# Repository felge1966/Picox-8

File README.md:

PicoX-8: Universalerweiterung für den Epson PX-8

https://forum.classic-computing.de/forum/index.php?thread/33295-picox-8-universalerweiterung-f%C3%BCr-den-epson-px-8/

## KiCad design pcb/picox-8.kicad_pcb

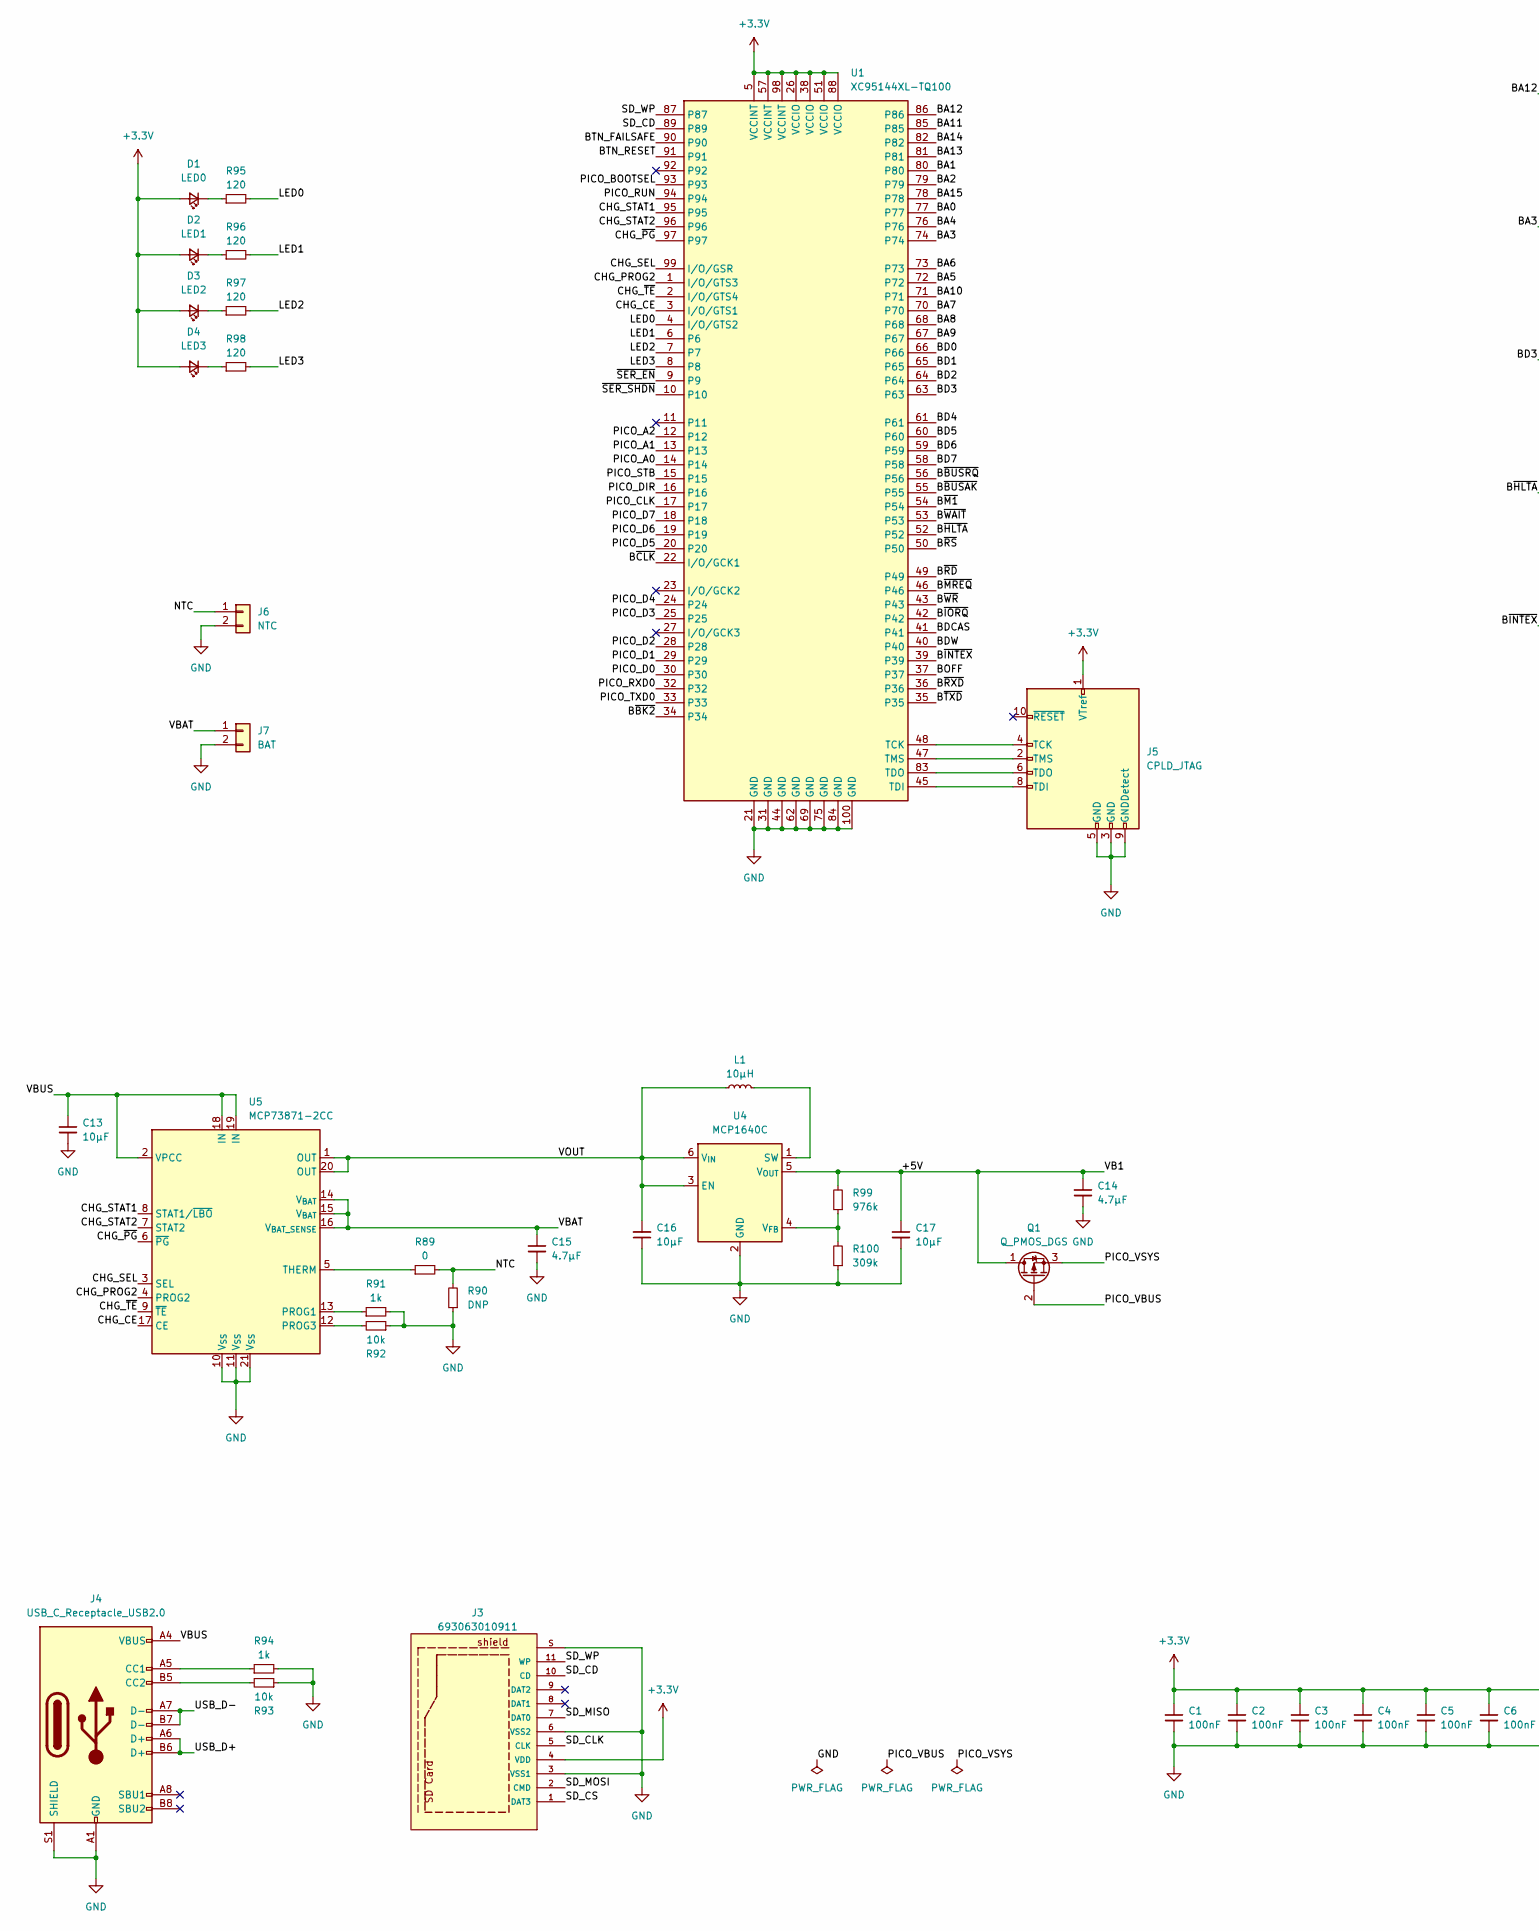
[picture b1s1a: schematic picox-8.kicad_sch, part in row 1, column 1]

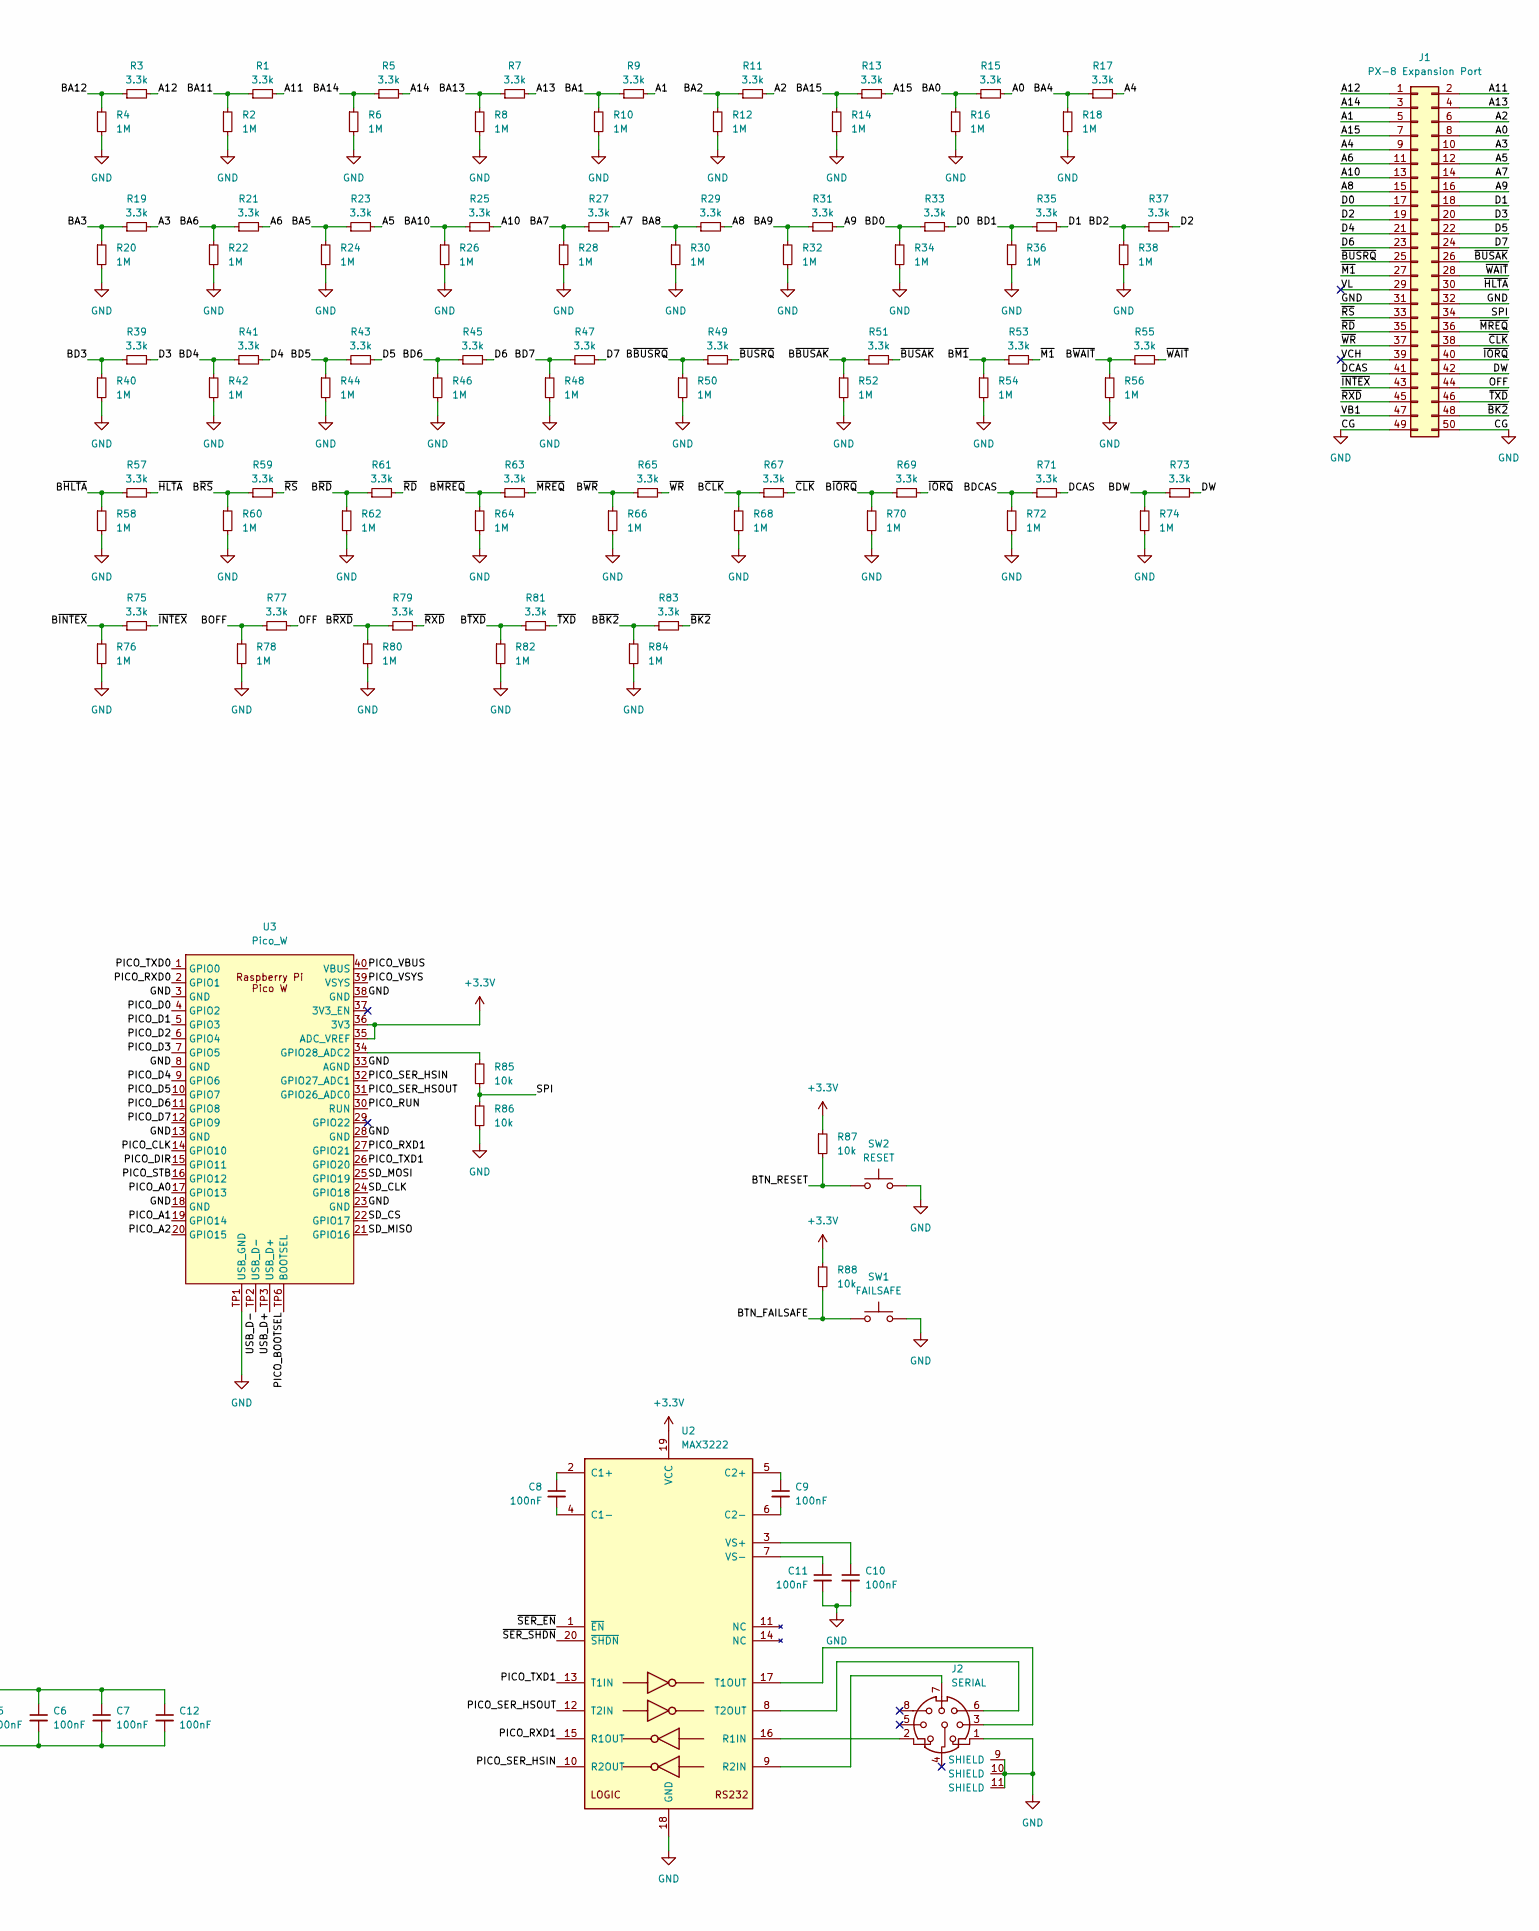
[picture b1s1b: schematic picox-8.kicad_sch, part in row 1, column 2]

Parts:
C1, C2, C3, C4, C5, C6, C7, C8, C9, C10, C11, C12: 100nF; C_0603_1608Metric_Pad1.08x0.95mm_HandSolder
C13, C16, C17: 10μF; C_0603_1608Metric_Pad1.08x0.95mm_HandSolder
C14, C15: 4.7μF; C_0603_1608Metric_Pad1.08x0.95mm_HandSolder
D1: LED0; LED_0603_1608Metric_Pad1.05x0.95mm_HandSolder
D2: LED1; LED_0603_1608Metric_Pad1.05x0.95mm_HandSolder
D3: LED2; LED_0603_1608Metric_Pad1.05x0.95mm_HandSolder
D4: LED3; LED_0603_1608Metric_Pad1.05x0.95mm_HandSolder
J1: PX-8 Expansion Port; IDC-Header_2x25_P2.54mm_Latch_Horizontal
J2: SERIAL; minidin-8
J3: 693063010911; Wuerth SD Card 693063010911; PART-NUMBER 693063010911
J4: USB_C_Receptacle_USB2.0; USB_C_Receptacle_G-Switch_GT-USB-7010ASV
J5: CPLD_JTAG; IDC-Header_2x05_P2.54mm_Vertical
J6: NTC; PinHeader_1x02_P2.54mm_Vertical
J7: BAT; JST_EH_S2B-EH_1x02_P2.50mm_Horizontal
L1: 10µH; L_Radial_D6.0mm_P4.00mm
Q1: Q_PMOS_DGS; SOT-23-3
R1, R3, R5, R7, R9, R11, R13, R15, R17, R19, R21, R23, R25, R27, R29, R31, R33, R35, R37, R39, R41, R43, R45, R47, R49, R51, R53, R55, R57, R59, R61, R63, R65, R67, R69, R71, R73, R75, R77, R79, R81, R83: 3.3k; R_0603_1608Metric_Pad0.98x0.95mm_HandSolder
R2, R4, R6, R8, R10, R12, R14, R16, R18, R20, R22, R24, R26, R28, R30, R32, R34, R36, R38, R40, R42, R44, R46, R48, R50, R52, R54, R56, R58, R60, R62, R64, R66, R68, R70, R72, R74, R76, R78, R80, R82, R84: 1M; R_0603_1608Metric_Pad0.98x0.95mm_HandSolder
R85, R86, R87, R88, R92, R93: 10k; R_0603_1608Metric_Pad0.98x0.95mm_HandSolder
R89: 0; R_0603_1608Metric_Pad0.98x0.95mm_HandSolder
R90: DNP; R_0603_1608Metric_Pad0.98x0.95mm_HandSolder
R91, R94: 1k; R_0603_1608Metric_Pad0.98x0.95mm_HandSolder
R95, R96, R97, R98: 120; R_0603_1608Metric_Pad0.98x0.95mm_HandSolder
R99: 976k; R_0603_1608Metric_Pad0.98x0.95mm_HandSolder
R100: 309k; R_0603_1608Metric_Pad0.98x0.95mm_HandSolder
SW1: FAILSAFE; SW_Tactile_SPST_Angled_PTS645Vx39-2LFS
SW2: RESET; SW_Tactile_SPST_Angled_PTS645Vx39-2LFS
U1: XC95144XL-TQ100; TQFP-100_14x14mm_P0.5mm
U2: MAX3222; TSSOP-20_4.4x6.5mm_P0.65mm
U3: Pico_W; RPI Pico W USB and Prog
U4: MCP1640C; SOT-23-6
U5: MCP73871-2CC; QFN-20-1EP_4x4mm_P0.5mm_EP2.5x2.5mm

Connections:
+3.3V: C1.1, C2.1, C3.1, C4.1, C5.1, C6.1, C7.1, C12.1, D1.2 (A), D2.2 (A), D3.2 (A), D4.2 (A), J3.4 (VDD), J5.1 (VTref), R87.1, R88.1, U1.5 (VCCINT), U1.26 (VCCIO), U1.38 (VCCIO), U1.51 (VCCIO), U1.57 (VCCINT), U1.88 (VCCIO), U1.98 (VCCINT), U2.19 (VCC), U3.35 (ADC_VREF), U3.36 (3V3)
/+5V: C14.1, C17.1, J1.47 (VB1), Q1.1 (D), R99.2, U4.5 (V_{OUT})
/A0: J1.8 (A0), R15.2
/A1: J1.5 (A1), R9.2
/A2: J1.6 (A2), R11.2
/A3: J1.10 (A3), R19.2
/A4: J1.9 (A4), R17.2
/A5: J1.12 (A5), R23.2
/A6: J1.11 (A6), R21.2
/A7: J1.14 (A7), R27.2
/A8: J1.15 (A8), R29.2
/A9: J1.16 (A9), R31.2
/A10: J1.13 (A10), R25.2
/A11: J1.2 (A11), R1.2
/A12: J1.1 (A12), R3.2
/A13: J1.4 (A13), R7.2
/A14: J1.3 (A13), R5.2
/A15: J1.7 (A15), R13.2
/BA0: R15.1, R16.1, U1.77
/BA1: R9.1, R10.1, U1.80
/BA2: R11.1, R12.1, U1.79
/BA3: R19.1, R20.1, U1.74
/BA4: R17.1, R18.1, U1.76
/BA5: R23.1, R24.1, U1.72
/BA6: R21.1, R22.1, U1.73
/BA7: R27.1, R28.1, U1.70
/BA8: R29.1, R30.1, U1.68
/BA9: R31.1, R32.1, U1.67
/BA10: R25.1, R26.1, U1.71
/BA11: R1.1, R2.1, U1.85
/BA12: R3.1, R4.1, U1.86
/BA13: R7.1, R8.1, U1.81
/BA14: R5.1, R6.1, U1.82
/BA15: R13.1, R14.1, U1.78
/BD0: R33.1, R34.1, U1.66
/BD1: R35.1, R36.1, U1.65
/BD2: R37.1, R38.1, U1.64
/BD3: R39.1, R40.1, U1.63
/BD4: R41.1, R42.1, U1.61
/BD5: R43.1, R44.1, U1.60
/BD6: R45.1, R46.1, U1.59
/BD7: R47.1, R48.1, U1.58
/BDCAS: R71.1, R72.1, U1.41
/BDW: R73.1, R74.1, U1.40
/BOFF: R77.1, R78.1, U1.37
/BTN_FAILSAFE: R88.2, SW1.1, U1.90
/BTN_RESET: R87.2, SW2.1, U1.91
/B~BK2: R83.1, R84.1, U1.34
/B~BUSAK: R51.1, R52.1, U1.55
/B~BUSRQ: R49.1, R50.1, U1.56
/B~CLK: R67.1, R68.1, U1.22 (I/O/GCK1)
/B~HLTA: R57.1, R58.1, U1.52
/B~INTEX: R75.1, R76.1, U1.39
/B~IORQ: R69.1, R70.1, U1.42
/B~M1: R53.1, R54.1, U1.54
/B~MREQ: R63.1, R64.1, U1.46
/B~RD: R61.1, R62.1, U1.49
/B~RS: R59.1, R60.1, U1.50
/B~RXD: R79.1, R80.1, U1.36
/B~TXD: R81.1, R82.1, U1.35
/B~WAIT: R55.1, R56.1, U1.53
/B~WR: R65.1, R66.1, U1.43
/CHG_CE: U1.3 (I/O/GTS1), U5.17 (CE)
/CHG_PROG2: U1.1 (I/O/GTS3), U5.4 (PROG2)
/CHG_SEL: U1.99 (I/O/GSR), U5.3 (SEL)
/CHG_STAT1: U1.95, U5.8 (STAT1/~LBO)
/CHG_STAT2: U1.96, U5.7 (STAT2)
/CHG_~PG: U1.97, U5.6 (~PG)
/CHG_~TE: U1.2 (I/O/GTS4), U5.9 (~TE)
/D0: J1.17 (D0), R33.2
/D1: J1.18 (D1), R35.2
/D2: J1.19 (D2), R37.2
/D3: J1.20 (D3), R39.2
/D4: J1.21 (D4), R41.2
/D5: J1.22 (D5), R43.2
/D6: J1.23 (D6), R45.2
/D7: J1.24 (D7), R47.2
/DCAS: J1.41 (DCAS), R71.2
/DW: J1.42 (DW), R73.2
/LED0: R95.2, U1.4 (I/O/GTS2)
/LED1: R96.2, U1.6
/LED2: R97.2, U1.7
/LED3: R98.2, U1.8
/NTC: J6.1, R89.2, R90.2
/OFF: J1.44 (OFF), R77.2
/PICO_A0: U1.14, U3.17 (GPIO13)
/PICO_A1: U1.13, U3.19 (GPIO14)
/PICO_A2: U1.12, U3.20 (GPIO15)
/PICO_BOOTSEL: U1.93, U3.TP6 (BOOTSEL)
/PICO_CLK: U1.17, U3.14 (GPIO10)
/PICO_D0: U1.30, U3.4 (GPIO2)
/PICO_D1: U1.29, U3.5 (GPIO3)
/PICO_D2: U1.28, U3.6 (GPIO4)
/PICO_D3: U1.25, U3.7 (GPIO5)
/PICO_D4: U1.24, U3.9 (GPIO6)
/PICO_D5: U1.20, U3.10 (GPIO7)
/PICO_D6: U1.19, U3.11 (GPIO8)
/PICO_D7: U1.18, U3.12 (GPIO9)
/PICO_DIR: U1.16, U3.15 (GPIO11)
/PICO_RUN: U1.94, U3.30 (RUN)
/PICO_RXD0: U1.32, U3.2 (GPIO1)
/PICO_RXD1: U2.15 (R1OUT), U3.27 (GPIO21)
/PICO_SER_HSIN: U2.10 (R2OUT), U3.32 (GPIO27_ADC1)
/PICO_SER_HSOUT: U2.12 (T2IN), U3.31 (GPIO26_ADC0)
/PICO_STB: U1.15, U3.16 (GPIO12)
/PICO_TXD0: U1.33, U3.1 (GPIO0)
/PICO_TXD1: U2.13 (T1IN), U3.26 (GPIO20)
/PICO_VBUS: Q1.2 (G), U3.40 (VBUS)
/PICO_VSYS: Q1.3 (S), U3.39 (VSYS)
/SD_CD: J3.10 (CD), U1.89
/SD_CLK: J3.5 (CLK), U3.24 (GPIO18)
/SD_CS: J3.1 (DAT3), U3.22 (GPIO17)
/SD_MISO: J3.7 (DAT0), U3.21 (GPIO16)
/SD_MOSI: J3.2 (CMD), U3.25 (GPIO19)
/SD_WP: J3.11 (WP), U1.87
/SPI: J1.34 (SPI), R85.2, R86.1
/USB_D+: J4.A6 (D+), J4.B6 (D+), U3.TP3 (USB_D+)
/USB_D-: J4.A7 (D-), J4.B7 (D-), U3.TP2 (USB_D-)
/VBAT: C15.1, J7.1, U5.14 (V_{BAT}), U5.15 (V_{BAT}), U5.16 (V_{BAT_SENSE})
/VBUS: C13.1, J4.A4 (VBUS), J4.A9 (VBUS), J4.B4 (VBUS), J4.B9 (VBUS), U5.2 (VPCC), U5.18 (IN), U5.19 (IN)
/VCH: J1.39 (VCH)
/VL: J1.29 (VL)
/VOUT: C16.2, L1.1, U4.3 (EN), U4.6 (V_{IN}), U5.1 (OUT), U5.20 (OUT)
/~BK2: J1.48 (~BK2), R83.2
/~BUSAK: J1.26 (~BUSAK), R51.2
/~BUSRQ: J1.25 (~BUSRQ), R49.2
/~CLK: J1.38 (~CLK), R67.2
/~HLTA: J1.30 (~HLTA), R57.2
/~INTEX: J1.43 (~INTEX), R75.2
/~IORQ: J1.40 (~IORQ), R69.2
/~M1: J1.27 (~M1), R53.2
/~MREQ: J1.36 (~MREQ), R63.2
/~RD: J1.35 (~RD), R61.2
/~RS: J1.33 (~RESET), R59.2
/~RXD: J1.45 (~RXD), R79.2
/~SER_EN: U1.9, U2.1 (~EN)
/~SER_SHDN: U1.10, U2.20 (~SHDN)
/~TXD: J1.46 (~TXD), R81.2
/~WAIT: J1.28 (~WAIT), R55.2
/~WR: J1.37 (~WR), R65.2
GND: C1.2, C2.2, C3.2, C4.2, C5.2, C6.2, C7.2, C10.2, C11.2, C12.2, C13.2, C14.2, C15.2, C16.1, C17.2, J1.31 (GND), J1.32 (GND), J1.49 (CG), J1.50 (CG), J2.1, J2.9 (SHIELD), J2.10 (SHIELD), J2.11 (SHIELD), J3.3 (VSS1), J3.6 (VSS2), J3.S, J4.A1 (GND), J4.A12 (GND), J4.B1 (GND), J4.B12 (GND), J4.S1 (SHIELD), J5.3 (GND), J5.5 (GND), J5.9 (GNDDetect), J6.2, J7.2, R2.2, R4.2, R6.2, R8.2, R10.2, R12.2, R14.2, R16.2, R18.2, R20.2, R22.2, R24.2, R26.2, R28.2, R30.2, R32.2, R34.2, R36.2, R38.2, R40.2, R42.2, R44.2, R46.2, R48.2, R50.2, R52.2, R54.2, R56.2, R58.2, R60.2, R62.2, R64.2, R66.2, R68.2, R70.2, R72.2, R74.2, R76.2, R78.2, R80.2, R82.2, R84.2, R86.2, R90.1, R91.2, R92.1, R93.1, R94.2, R100.1, SW1.2, SW2.2, U1.21 (GND), U1.31 (GND), U1.44 (GND), U1.62 (GND), U1.69 (GND), U1.75 (GND), U1.84 (GND), U1.100 (GND), U2.18 (GND), U3.3 (GND), U3.8 (GND), U3.13 (GND), U3.18 (GND), U3.23 (GND), U3.28 (GND), U3.33 (AGND), U3.38 (GND), U3.TP1 (USB_GND), U4.2 (GND), U5.10 (V_{SS}), U5.11 (V_{SS}), U5.21 (V_{SS})
unnamed: D1.1 (K), R95.1
unnamed: D2.1 (K), R96.1
unnamed: D3.1 (K), R97.1
unnamed: D4.1 (K), R98.1
unnamed: J4.A5 (CC1), R94.1
unnamed: J4.B5 (CC2), R93.2
unnamed: J5.4 (TCK), U1.48 (TCK)
unnamed: J5.8 (TDI), U1.45 (TDI)
unnamed: J5.6 (TDO), U1.83 (TDO)
unnamed: J5.2 (TMS), U1.47 (TMS)
unnamed: C8.1, U2.2 (C1+)
unnamed: C8.2, U2.4 (C1-)
unnamed: C9.1, U2.5 (C2+)
unnamed: C9.2, U2.6 (C2-)
unnamed: J2.2, U2.16 (R1IN)
unnamed: J2.7, U2.9 (R2IN)
unnamed: J2.3, U2.17 (T1OUT)
unnamed: J2.6, U2.8 (T2OUT)
unnamed: C10.1, U2.3 (VS+)
unnamed: C11.1, U2.7 (VS-)
unnamed: R85.1, U3.34 (GPIO28_ADC2)
unnamed: L1.2, U4.1 (SW)
unnamed: R99.1, R100.2, U4.4 (V_{FB})
unnamed: R91.1, U5.13 (PROG1)
unnamed: R92.2, U5.12 (PROG3)
unnamed: R89.1, U5.5 (THERM)

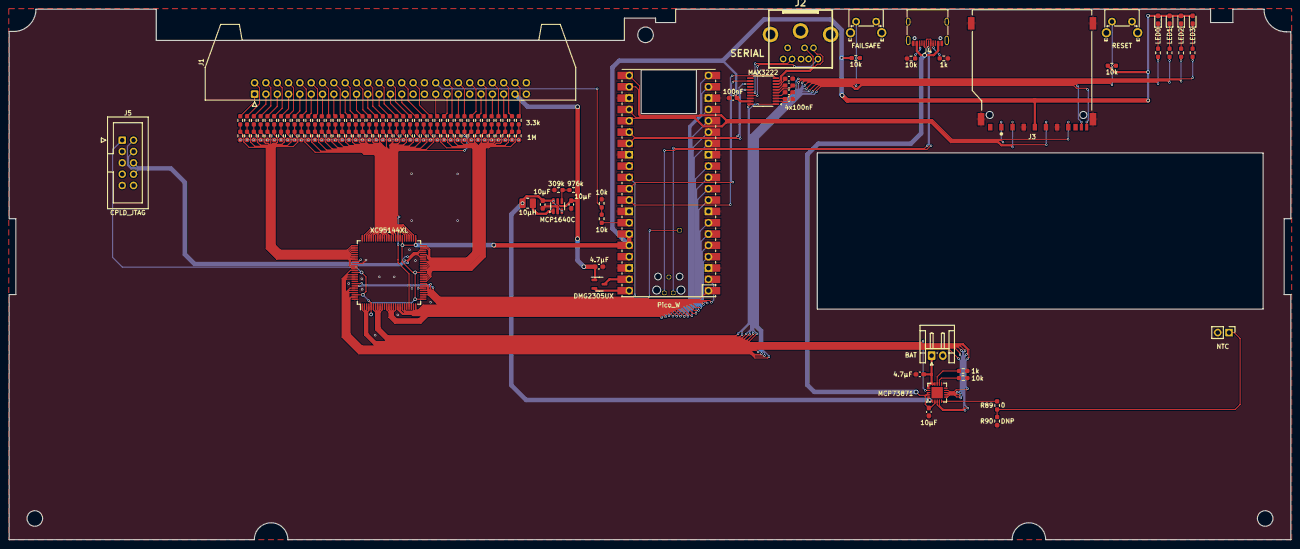
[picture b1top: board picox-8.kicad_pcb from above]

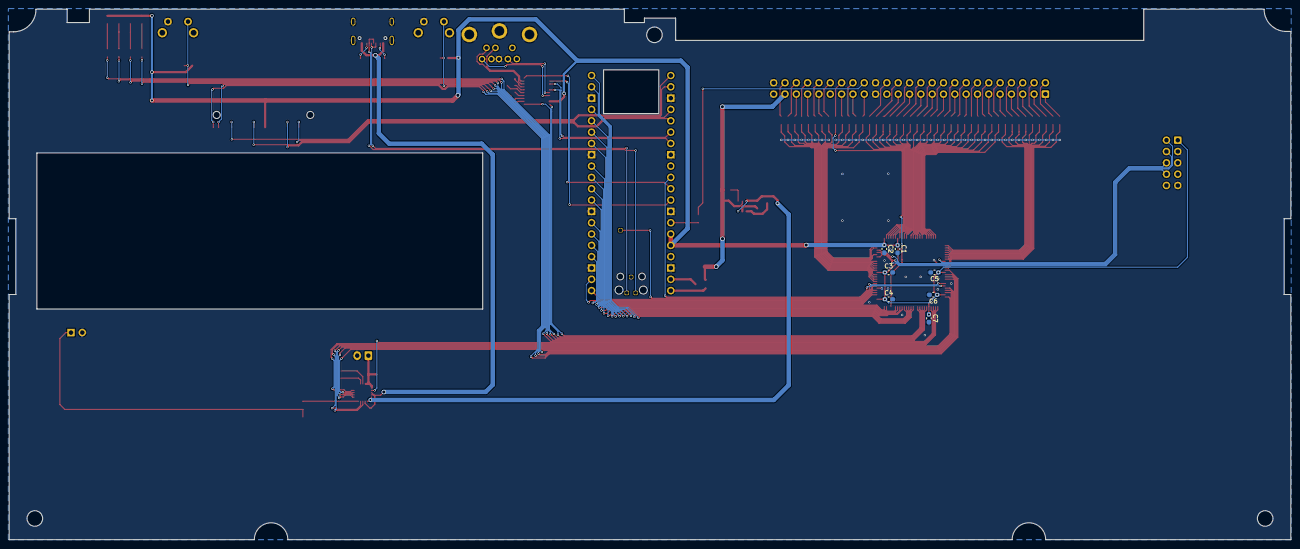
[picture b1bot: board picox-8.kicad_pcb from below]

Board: 2 copper layers, 287.5 x 119.0 mm, 137 parts (7 on the bottom side), 165 nets.

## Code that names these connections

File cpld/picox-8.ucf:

# Address bus (8-bit)
NET "address[0]"   LOC="77";
NET "address[1]"   LOC="80";
NET "address[10]"  LOC="71";
NET "address[11]"  LOC="85";
NET "address[12]"  LOC="86";
NET "address[13]"  LOC="81";
NET "address[14]"  LOC="82";
NET "address[15]"  LOC="78";
NET "address[2]"   LOC="79";
NET "address[3]"   LOC="74";
NET "address[4]"   LOC="76";
NET "address[5]"   LOC="72";
NET "address[6]"   LOC="73";
NET "address[7]"   LOC="70";
NET "address[8]"   LOC="68";
NET "address[9]"   LOC="67";

# Data bus (8-bit)
NET "data[0]"      LOC="66";
NET "data[1]"      LOC="65";
NET "data[2]"      LOC="64";
NET "data[3]"      LOC="63";
NET "data[4]"      LOC="61";
NET "data[5]"      LOC="60";
NET "data[6]"      LOC="59";
NET "data[7]"      LOC="58";

# Z80 Control
NET "clk"          LOC="22" | PERIOD = 408.16 ns HIGH 50%;
NET "iorq_n"       LOC="42";
NET "rd_n"         LOC="49";
NET "wr_n"         LOC="43";
NET "rs_n"         LOC="50";
NET "busak_n"      LOC="55";
NET "busrq_n"      LOC="56";
NET "hlta_n"       LOC="52";
NET "intex_n"      LOC="39";

# Serial port
NET "rxd_n"        LOC="36";
NET "txd_n"        LOC="35";
NET "m1_n"         LOC="54";
NET "mreq_n"       LOC="46";
NET "wait_n"       LOC="53";

# Other PX-8 bus signals
NET "dcas"         LOC="41";
NET "dw"           LOC="40";
NET "off"          LOC="37";
NET "bk2_n"        LOC="34";

# Pico register access port
NET "pico_data[0]" LOC="30"; # Pico GP2
NET "pico_data[1]" LOC="29"; # Pico GP3
NET "pico_data[2]" LOC="28"; # Pico GP4
NET "pico_data[3]" LOC="25"; # Pico GP5
NET "pico_data[4]" LOC="24"; # Pico GP6
NET "pico_data[5]" LOC="20"; # Pico GP7
NET "pico_data[6]" LOC="19"; # Pico GP8
NET "pico_data[7]" LOC="18"; # Pico GP9

NET "pico_clk"     LOC="17"; # Pico GP10
NET "pico_dir"     LOC="16"; # Pico GP11
NET "pico_stb"     LOC="15"; # Pico GP12

NET "pico_addr[0]" LOC="14"; # Pico GP13
NET "pico_addr[1]" LOC="13"; # Pico GP14
NET "pico_addr[2]" LOC="12"; # Pico GP15

NET "pico_rxd0"    LOC="32";
NET "pico_txd0"    LOC="33";

NET "pico_bootsel" LOC="93";
NET "pico_run"     LOC="94";

# Serial transceiver control
NET "ser_en_n"     LOC="9";
NET "ser_shdn_n"   LOC="10";

# Battery charger control
NET "chg_ce"       LOC="3";
NET "chg_prog2"    LOC="1";
NET "chg_sel"      LOC="99";
NET "chg_stat1"    LOC="95";
NET "chg_stat2"    LOC="96";
NET "chg_pg_n"     LOC="97";
NET "chg_te_n"     LOC="2";

# SD Card status bits
NET "sd_cd"        LOC="89";
NET "sd_wp"        LOC="87";

# Buttons
NET "btn_failsafe" LOC="90";
NET "btn_reset"    LOC="91";

# Debugging LEDs
NET "led0"         LOC="4";
NET "led1"         LOC="6";
NET "led2"         LOC="7";
NET "led3"         LOC="8";

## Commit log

2024-07-06 try first version
2024-07-06 refactor vhdl
2024-07-06 rearrange pins
2024-07-07 serial port access with DAK Comm works
2024-07-08 add modem control register
2024-07-08 fix bugs
2024-07-09 switch to xc95144xl in tq100 package
2024-07-09 add ramdisk and modem control registers
2024-07-09 fix syntax errors
2024-07-09 synchronize on z80 clock
2024-07-09 refactor
2024-07-09 rename constants for clarity
2024-07-09 fix typo
2024-07-09 leds
2024-07-09 buffer leds so that they are initialized properly
2024-07-11 connect pico and cpld + start of firmware
2024-07-12 use pio
2024-07-12 seems to be working
2024-07-13 fix over-eager driving of data bus
2024-07-13 skip reading data when writing
2024-07-21 push around oe
2024-07-21 begin working on firmware
2024-07-22 debugging aids
2024-07-23 can read some bytes from px-8 (still missing first one)
2024-07-23 first somewhat working version
2024-07-23 add sample ramdisk image
2024-07-24 refactor and modularize
2024-07-24 can generate DTMF tones
2024-07-25 begin adding command processor
2024-07-25 some pcb progress
2024-07-25 simple line editor
2024-07-25 Implement command processor
2024-07-25 command processor, simple config
2024-07-26 improve cli
2024-07-26 wifi setup
2024-07-26 wifi tweaks
2024-07-27 modem connections work
2024-07-27 switch off tone generators when resetting modem
2024-07-27 improve command mode timing & baud rate detection
2024-07-28 implement telnet option negotiation
2024-07-28 process in-line telnet options
2024-07-28 comment
2024-07-28 Add searchable PX-8 manuals
2024-07-28 move irqs into cpld register to free gpios
2024-07-28 add sdcard.py
2024-07-28 SD-Card storage, wip
2024-07-28 complete version of the os reference manual
2024-07-29 improve ramdisk image handling
2024-07-29 diskdef entry for cpmtools to access ramdisk images
2024-07-29 roms and tools
2024-07-29 work on rom extraction tools
2024-07-29 remove debug output
2024-07-29 begin floppy emu work
2024-07-30 Revert "begin floppy emu work"
    This reverts commit 6f094f93f455c5c3878d0fb23ed54a7a5adb0054.
2024-07-30 drop rom reading tools
    there is https://github.com/NaturalTangent/epson_rom_tools instead
2024-07-30 turbo pascal
2024-07-30 reorganize software collection
2024-07-30 software cleanup
2024-07-31 delay modem reset when disabled
    this is to accommodate DAKCOMM's behavior
2024-07-31 sdcard error handling, modem power control
2024-07-31 echo uart data by default
2024-08-02 add disassembly project for system rom
2024-08-02 add bus current limiting and pull resistors
2024-08-02 bus buffer resistors
2024-08-02 hide resistor silkscreen markings
2024-08-03 PCB work
2024-08-06 max3222 datasheet
2024-08-06 schematics work: buttons hooked up
2024-08-06 cpld & pcb work
2024-08-09 schematic nearing completion
2024-08-10 erc fixes
2024-08-10 layout work
2024-08-11 routing complete
2024-08-11 remove kiutils based script as it does not support kicad 8
2024-08-12 more pcb work
2024-08-12 add mrequests as submodule
2024-08-12 implement fail-safe mode
2024-08-12 telnet server can't do a lot now
2024-08-15 prototype hardware support re-added
2024-08-31 tools to extract cpld pins from schematic
2024-08-31 Adapt to v1 PCB
2024-08-31 charger & serial port signals setup
2024-08-31 rom patching
2024-08-31 first version sent to jlcpcb for production
2024-08-31 add telnet mode state
2024-08-31 adapt to pcb-1
2024-09-14 some life is in the board
